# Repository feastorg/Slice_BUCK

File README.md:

# Buck Converter / Analog Signal Generator Slice

Buck Converter / Analog Signal Generator Slice for BREAD.

## Introduction

A programmable DC supply on one slice: a P-FET high-side buck stage takes the
backplane's 12 V bus and gives 0-12 V on J2, set over serial and regulated by the
Nano on A0.

## Ratings

| | |
|---|---|
| Input | +12 V bus through J1 (pins 2 and 9). Nothing else. |
| Output | 0-12 V on J2 (pin 1 +, pin 2 GNDPWR). In regulation up to about 11 V at 3 A; above that the stage goes to 100 % duty, 11.7 V into 4 ohm (2.9 A) in simulation. |
| Current | Up to 3 A out. At 100 % duty the bus carries the full load current, 3 A, which is the per-slot budget. |
| Switching | 31.25 kHz from the Nano's D9 (Timer1). |
| Feedback | Vout through 20.0k / 10.0k to A0, so 12 V out reads 4.00 V. |

**12 V bus only.** The gate drive is the input voltage: with Q1 on, its gate sits
about 0.7 V above ground, so Vgs is about -(Vin - 0.7 V). The DMP6023LE is rated
for +/-20 V gate-source, so this stage must not be fed from a 24 V bus. A bus
clamped at 15 V still gives -14.3 V, inside the rating.

**The output is regulated by firmware, not by the hardware.** At light load the
stage runs discontinuous and the output rises toward the input at any fixed duty:
in simulation 50 % duty gives 5.8 V into 4 ohm and 10.9 V into 1 kohm. Use SETV,
which regulates on A0. R9 (1k) keeps a minimum load so low voltages stay
regulable with nothing connected. The shortest on-time the stage makes is about
0.45 us (simulation), so with nothing else connected the lowest steady output is
about 1.4 V; SETV below that holds the average by toggling between that pulse and off.

At reset, or with no sketch running, D9 floats and Q1 stays off (R3 holds Q3 off,
R4 pulls the driver to +12 V).

## Usage

Serial at 115200 baud, one command per line:

| Command | Does |
|---|---|
| `ON` | Enable the output (resumes SETV regulation or the last SET duty). |
| `OFF` | Disable the output (D9 low, Q1 off). |
| `SETV <0-12>` | Regulate Vout to this many volts. The setpoint ramps at 5 V/s. |
| `SET <0-255>` | Open-loop duty (0-255 scaled onto the 9-bit timer); leaves SETV. |
| `SETTOP <ohm>` | Calibrate the divider's top resistor (default 20000). |
| `STATUS` | Print the state; also printed once a second. |

Over-voltage cut-off: if Vout stays above 13 V, or more than 1 V above the SETV
setpoint while the stage is still switching, for 50 ms, the output turns off and
the sketch prints `ERR: OV`. Send `ON` to restart.

## Documentation

Please refer to the [docs](/docs) for more info.

The switch stage has a SPICE check in `hardware/sim/`: run `python3 hardware/sim/check.py`
from the repo root with `kicad-cli` and `ngspice` on PATH.

---

<div align="center">
  
</div>

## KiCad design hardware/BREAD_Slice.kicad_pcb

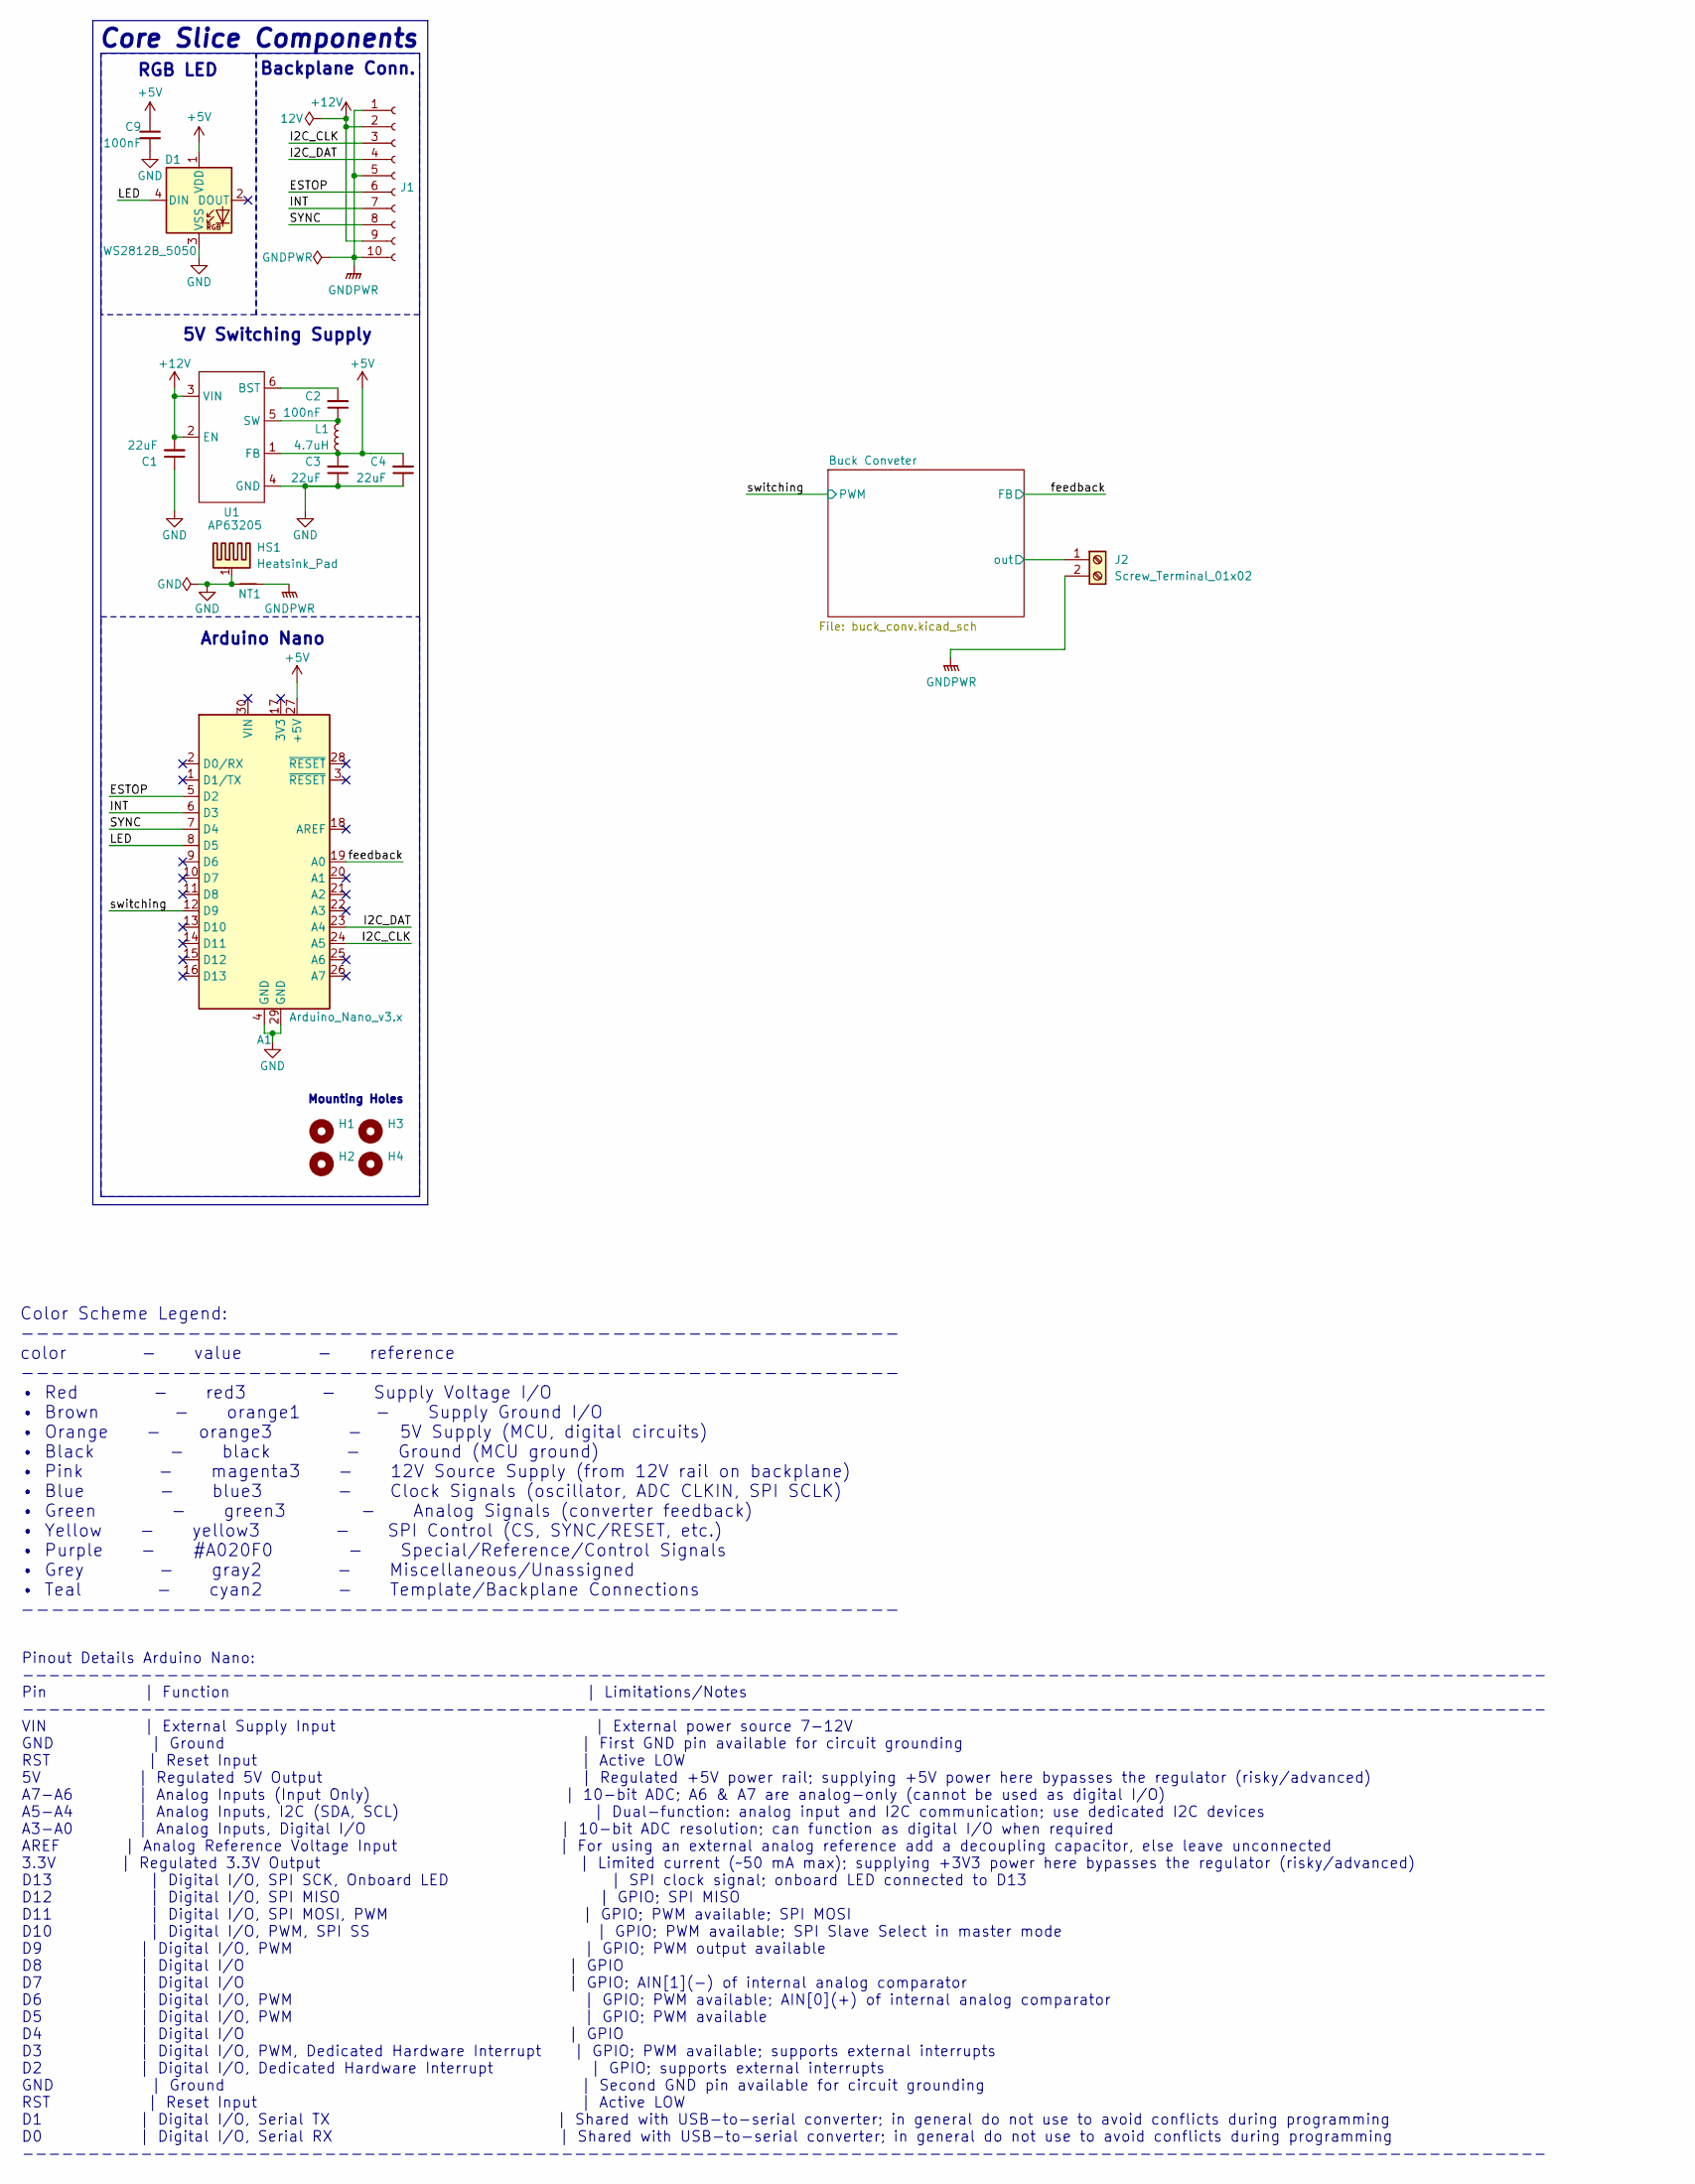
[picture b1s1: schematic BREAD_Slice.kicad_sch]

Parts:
A1: Arduino_Nano_v3.x; Arduino_Nano
C1, C3, C4: 22uF; C_1206_3216Metric
C2: 100nF; C_1206_3216Metric
C9: 100nF; C_0805_2012Metric; MPN CL21B104KBCNNNC
D1: WS2812B_5050; WS2812-5050-4PIN
H1, H2, H3, H4: MountingHole; MountingHole_5mm
HS1: Heatsink_Pad; Thermal_Pad
J1: Conn_01x10_Female; PinSocket_1x10_P2.54mm_Horizontal
J2: Screw_Terminal_01x02; TerminalBlock_4Ucon_1x02_P3.50mm_Horizontal
L1: 4.7uH; L_1210_3225Metric
NT1: NetTie_2; NetTie-2_SMD_Pad2.0mm
U1: AP63205; TSOT-23-6

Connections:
+5V: A1.27 (+5V), C3.2, C4.2, C9.1, D1.1 (VDD), L1.2, U1.1 (FB)
+12V: C1.2, J1.2, J1.9, U1.2 (EN), U1.3 (VIN); also elsewhere on the board
/Buck Conveter/out: J2.1; also elsewhere on the board
/ESTOP: A1.5 (D2), J1.6
/I2C_CLK: A1.24 (A5), J1.3
/I2C_DAT: A1.23 (A4), J1.4
/INT: A1.6 (D3), J1.7
/LED: A1.8 (D5), D1.4 (DIN)
/SYNC: A1.7 (D4), J1.8
/feedback: A1.19 (A0); also elsewhere on the board
/switching: A1.12 (D9); also elsewhere on the board
GND: A1.4 (GND), A1.29 (GND), C1.1, C3.1, C4.1, C9.2, D1.3 (VSS), HS1.1, NT1.1, U1.4 (GND); also elsewhere on the board
GNDPWR: J1.1, J1.5, J1.10, J2.2, NT1.2; also elsewhere on the board
unnamed: C2.2, U1.6 (BST)
unnamed: C2.1, L1.1, U1.5 (SW)

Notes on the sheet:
5V Switching Supply
Pinout Details Arduino Nano: -------------------------------------------------------------------------------------------------------------------- Pin | Function | Limitations/Notes -------------------------------------------------------------------------------------------------------------------- V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
RGB LED
Color Scheme Legend: ---------------------------------------------------------- color - value - reference ---------------------------------------------------------- • Red - red3 - Supply Voltage I/O • Brown - orange1 - Supply Ground I/O • Orange - orange3 - 5V Supply (MCU, digital circuits) • Black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
Core Slice Components
Arduino Nano
Mounting Holes
Backplane Conn.

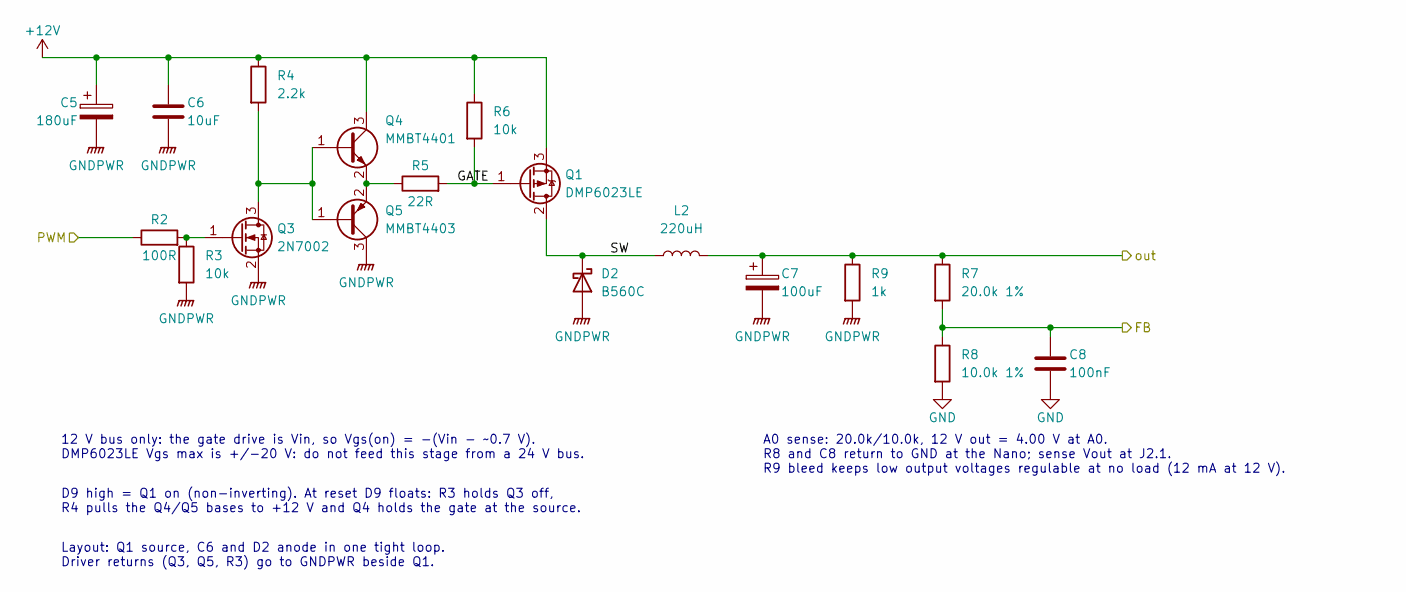
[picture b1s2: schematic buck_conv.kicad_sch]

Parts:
C5: 180uF; C_Radial_D8.0mm_H11.5mm_P3.50mm; MPN RNU1E181MDN1
C6: 10uF; C_1206_3216Metric; MPN GRM31CR71E106KA12L
C7: 100uF; C_Radial_D8.0mm_H11.5mm_P3.50mm
C8: 100nF; C_0805_2012Metric; MPN CL21B104KBCNNNC
D2: B560C; D_SMC; MPN B560C-13-F
L2: 220uH; L_Radial_D27.9mm_P19.05mm_Vishay_IHB-3; MPN 1130-221K-RC
Q1: DMP6023LE; SOT-223-3_TabPin2; MPN DMP6023LE-13
Q3: 2N7002; SOT-23; MPN 2N7002-7-F
Q4: MMBT4401; SOT-23; MPN MMBT4401-7-F
Q5: MMBT4403; SOT-23; MPN MMBT4403-7-F
R2: 100R; R_0805_2012Metric; MPN RC0805FR-07100RL
R3, R6: 10k; R_0805_2012Metric; MPN RC0805FR-0710KL
R4: 2.2k; R_1206_3216Metric; MPN RC1206FR-072K2L
R5: 22R; R_0805_2012Metric; MPN RC0805FR-0722RL
R7: 20.0k 1%; R_0805_2012Metric; MPN RC0805FR-0720KL
R8: 10.0k 1%; R_0805_2012Metric; MPN RC0805FR-0710KL
R9: 1k; R_2010_5025Metric; MPN RC2010FK-071KL

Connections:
+12V: C5.1, C6.1, Q1.3 (S), Q4.3 (C), R4.1, R6.1; also elsewhere on the board
/Buck Conveter/GATE: Q1.1 (G), R5.2, R6.2
/Buck Conveter/SW: D2.1 (K), L2.1, Q1.2 (D)
/Buck Conveter/out: C7.1, L2.2, R7.1, R9.1; also elsewhere on the board
/feedback: C8.1, R7.2, R8.1; also elsewhere on the board
/switching: R2.1; also elsewhere on the board
GND: C8.2, R8.2; also elsewhere on the board
GNDPWR: C5.2, C6.2, C7.2, D2.2 (A), Q3.2 (S), Q5.3 (C), R3.2, R9.2; also elsewhere on the board
unnamed: Q3.3 (D), Q4.1 (B), Q5.1 (B), R4.2
unnamed: Q3.1 (G), R2.2, R3.1
unnamed: Q4.2 (E), Q5.2 (E), R5.1

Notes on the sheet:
12 V bus only: the gate drive is Vin, so Vgs(on) = -(Vin - ~0.7 V). DMP6023LE Vgs max is +/-20 V: do not feed this stage from a 24 V bus.
D9 high = Q1 on (non-inverting). At reset D9 floats: R3 holds Q3 off, R4 pulls the Q4/Q5 bases to +12 V and Q4 holds the gate at the source.
Layout: Q1 source, C6 and D2 anode in one tight loop. Driver returns (Q3, Q5, R3) go to GNDPWR beside Q1.
A0 sense: 20.0k/10.0k, 12 V out = 4.00 V at A0. R8 and C8 return to GND at the Nano; sense Vout at J2.1. R9 bleed keeps low output voltages regulable at no load (12 mA at 12 V).

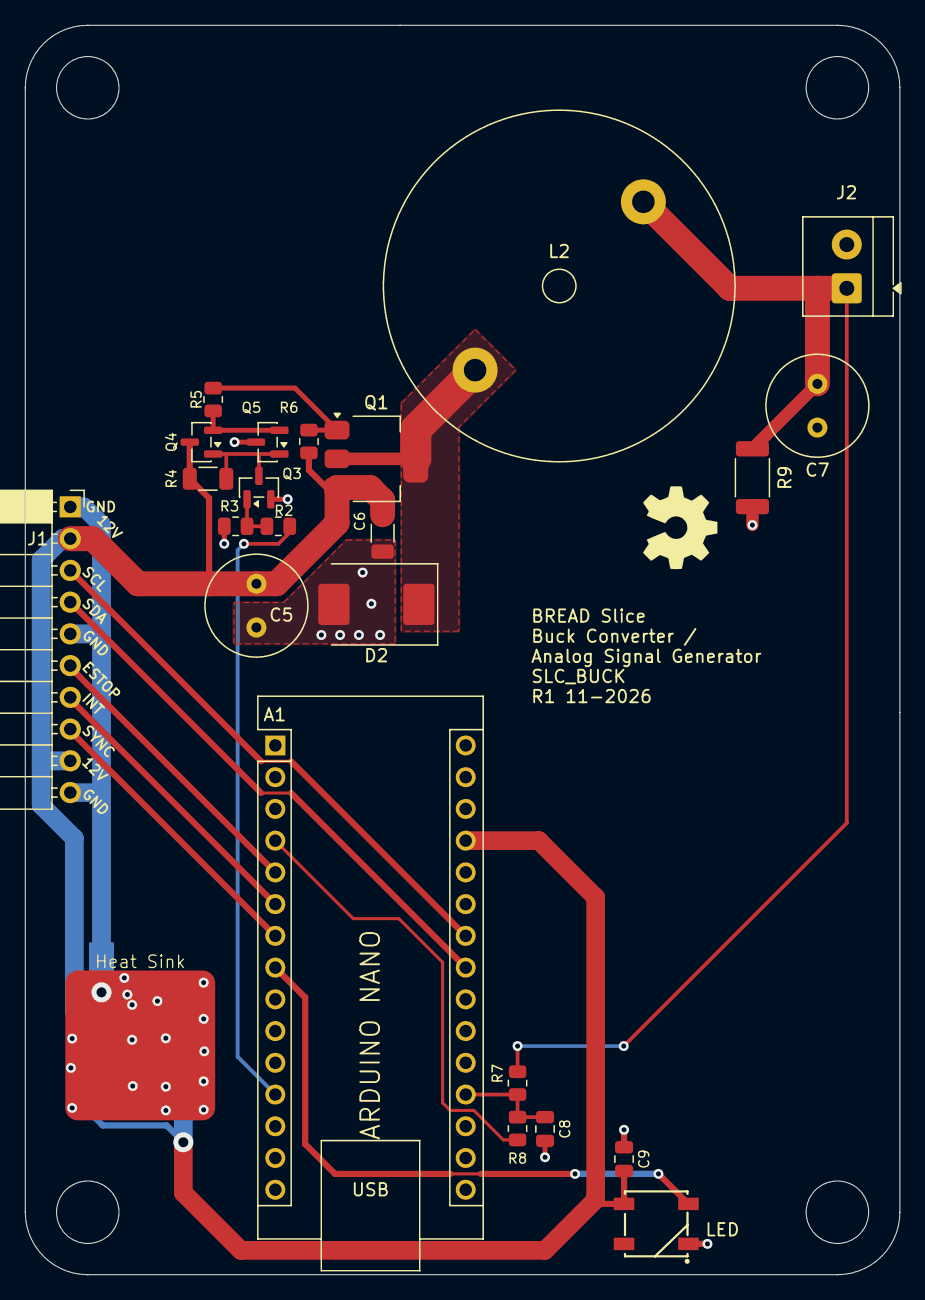
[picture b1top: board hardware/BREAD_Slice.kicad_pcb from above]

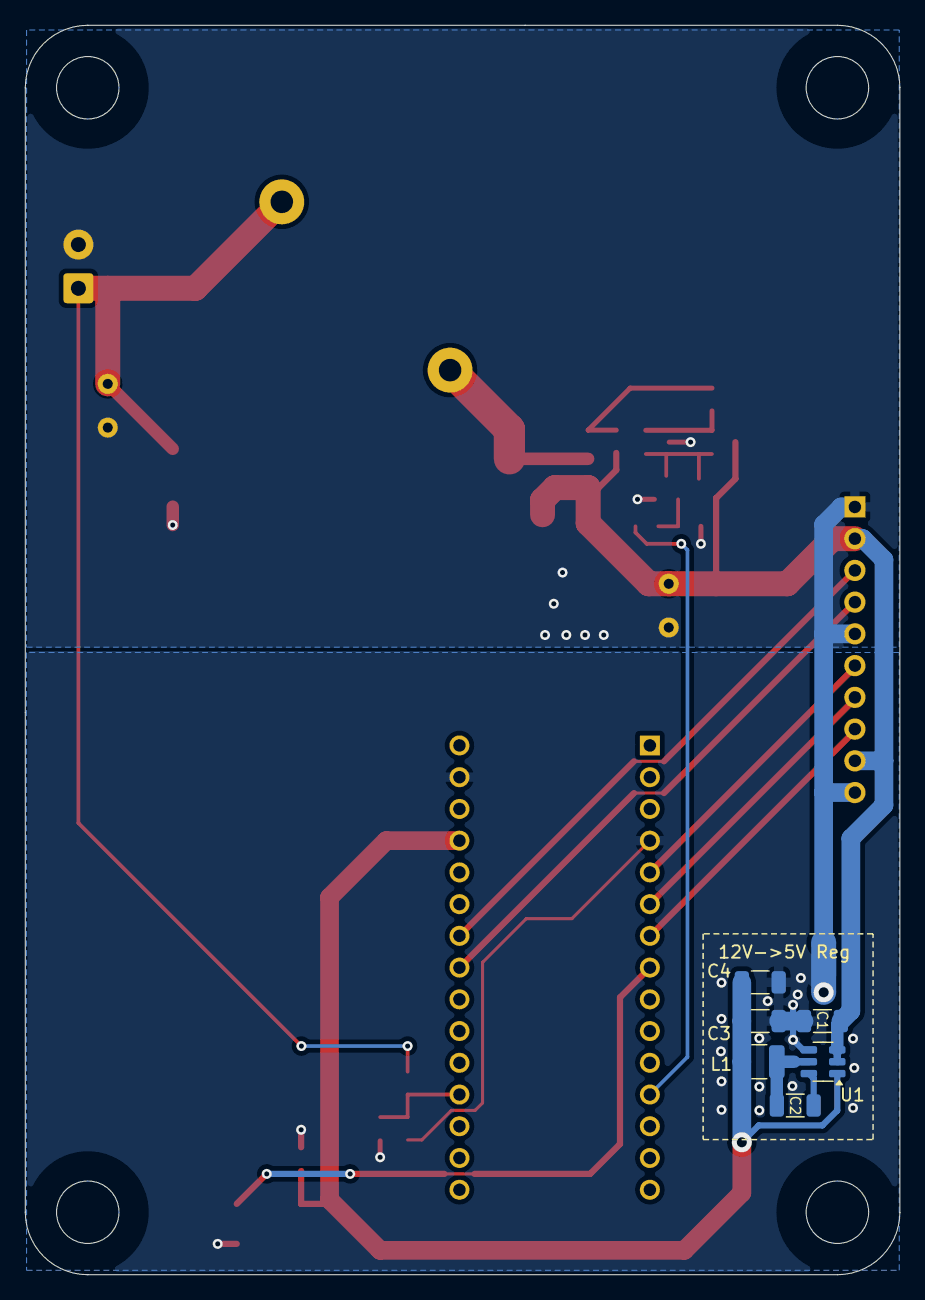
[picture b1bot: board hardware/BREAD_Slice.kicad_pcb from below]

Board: 2 copper layers, 70.0 x 100.0 mm, 36 parts (7 on the bottom side), 20 nets.

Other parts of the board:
Logo1: Logo_Open_Hardware_Small; OSHW-Symbol_6.7x6mm_SilkScreen

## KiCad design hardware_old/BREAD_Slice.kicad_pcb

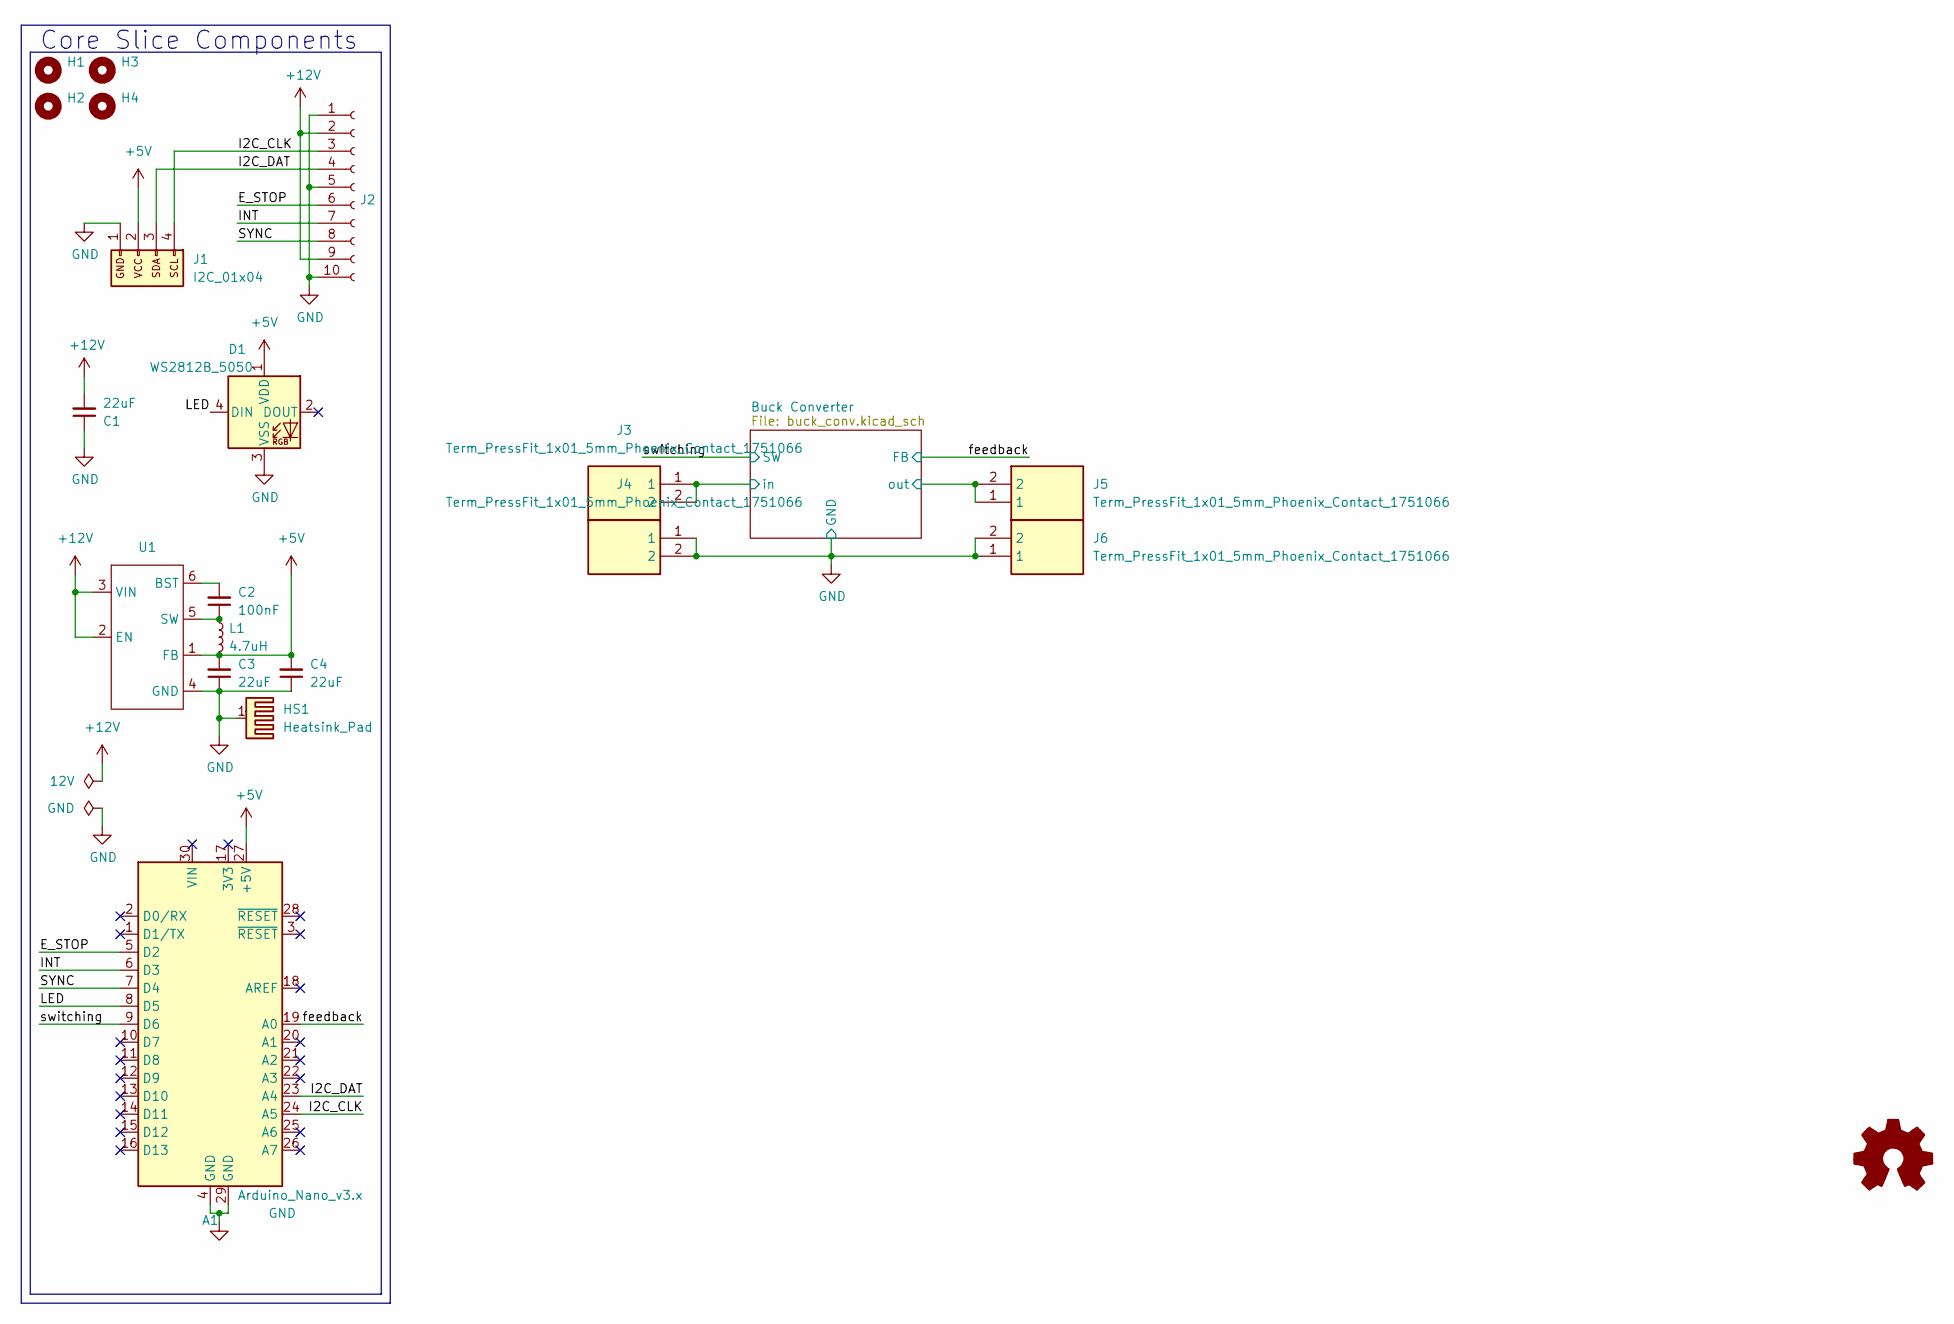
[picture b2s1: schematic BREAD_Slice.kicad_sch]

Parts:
A1: Arduino_Nano_v3.x; Arduino_Nano
C1, C3, C4: 22uF; C_1206_3216Metric
C2: 100nF; C_1206_3216Metric
D1: WS2812B_5050; WS2812-5050-4PIN
H1, H2, H3, H4: MountingHole; MountingHole_5mm
HS1: Heatsink_Pad; Thermal Pad
J1: I2C_01x04; JST_SH_SM04B-SRSS-TB_1x04-1MP_P1.00mm_Horizontal
J2: Conn_01x10_Female; PinSocket_1x10_P2.54mm_Horizontal
J3, J4, J5, J6: Term_PressFit_1x01_5mm_Phoenix_Contact_1751066; 1751066; Manufacturer_Part_Number 1751066
L1: 4.7uH; L_1210_3225Metric
U1: TSOT-23-6

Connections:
+5V: A1.27 (+5V), C3.2, C4.2, D1.1 (VDD), J1.2, L1.2, U1.1 (FB)
+12V: C1.2, J2.2, J2.9, U1.2 (EN), U1.3 (VIN)
/Buck Converter/in: J3.1, J3.2; also elsewhere on the board
/Buck Converter/out: J5.1, J5.2; also elsewhere on the board
/E_STOP: A1.5 (D2), J2.6
/I2C_CLK: A1.24 (A5), J1.4, J2.3
/I2C_DAT: A1.23 (A4), J1.3, J2.4
/INT: A1.6 (D3), J2.7
/LED: A1.8 (D5), D1.4 (DIN)
/SYNC: A1.7 (D4), J2.8
/feedback: A1.19 (A0); also elsewhere on the board
/switching: A1.9 (D6); also elsewhere on the board
GND: A1.4 (GND), A1.29 (GND), C1.1, C3.1, C4.1, D1.3 (VSS), HS1.1, J1.1, J2.1, J2.5, J2.10, J4.1, J4.2, J6.1, J6.2, U1.4 (GND); also elsewhere on the board
unnamed: C2.2, U1.6 (BST)
unnamed: C2.1, L1.1, U1.5 (SW)

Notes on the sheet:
Core Slice Components

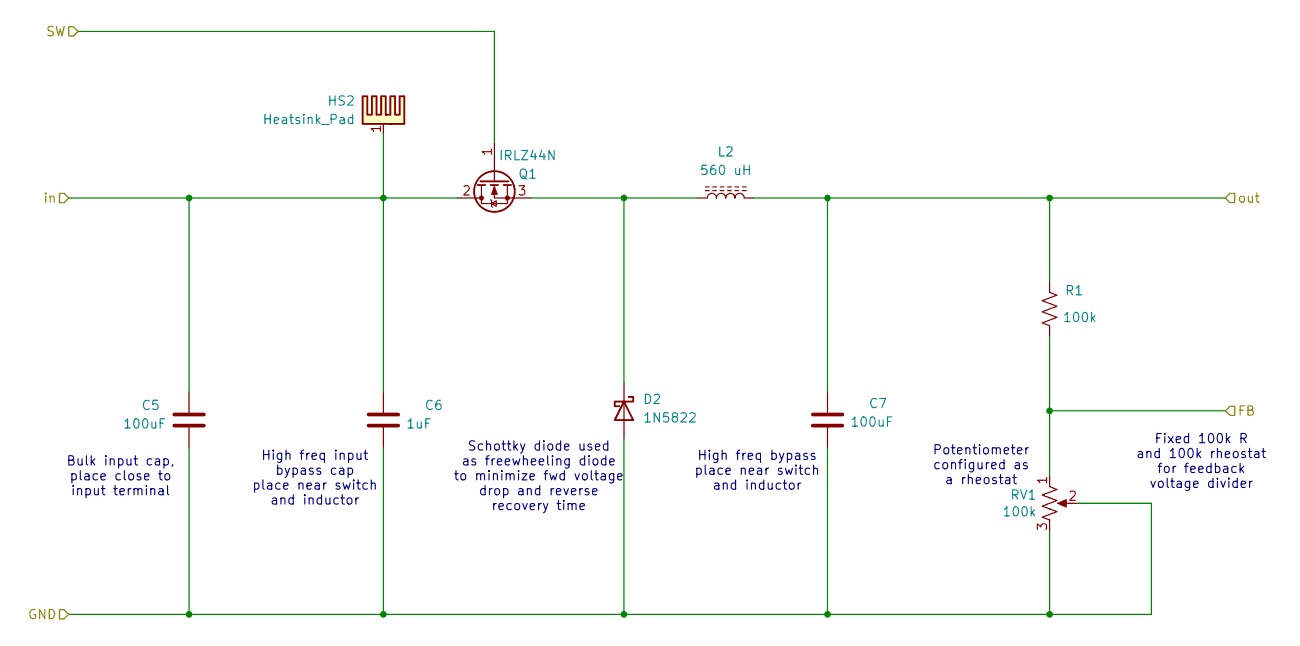
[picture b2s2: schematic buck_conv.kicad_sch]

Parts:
C5, C7: 100uF; C_Radial_D8.0mm_H11.5mm_P3.50mm
C6: 1uF; C_1206_3216Metric
D2: 1N5822; D_DO-201AD_P15.24mm_Horizontal
HS2: Heatsink_Pad; Thermal Pad
L2: 560 uH; L_Radial_D27.9mm_P19.05mm_Vishay_IHB-3
Q1: IRLZ44N; TO-220-3_Horizontal_TabDown
R1: 100k; R_Axial_DIN0309_L9.0mm_D3.2mm_P15.24mm_Horizontal
RV1: 100k; Potentiometer_Bourns_3266W_Vertical

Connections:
/Buck Converter/in: C5.1, C6.1, HS2.1, Q1.2 (D); also elsewhere on the board
/Buck Converter/out: C7.1, L2.2, R1.1; also elsewhere on the board
/feedback: R1.2, RV1.1; also elsewhere on the board
/switching: Q1.1 (G); also elsewhere on the board
GND: C5.2, C6.2, C7.2, D2.2 (A), RV1.2, RV1.3; also elsewhere on the board
unnamed: D2.1 (K), L2.1, Q1.3 (S)

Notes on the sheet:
Fixed 100k R and 100k rheostat for feedback voltage divider
Schottky diode used as freewheeling diode to minimize fwd voltage drop and reverse recovery time
Bulk input cap, place close to input terminal
High freq bypass place near switch and inductor
High freq input bypass cap place near switch and inductor
Potentiometer configured as a rheostat

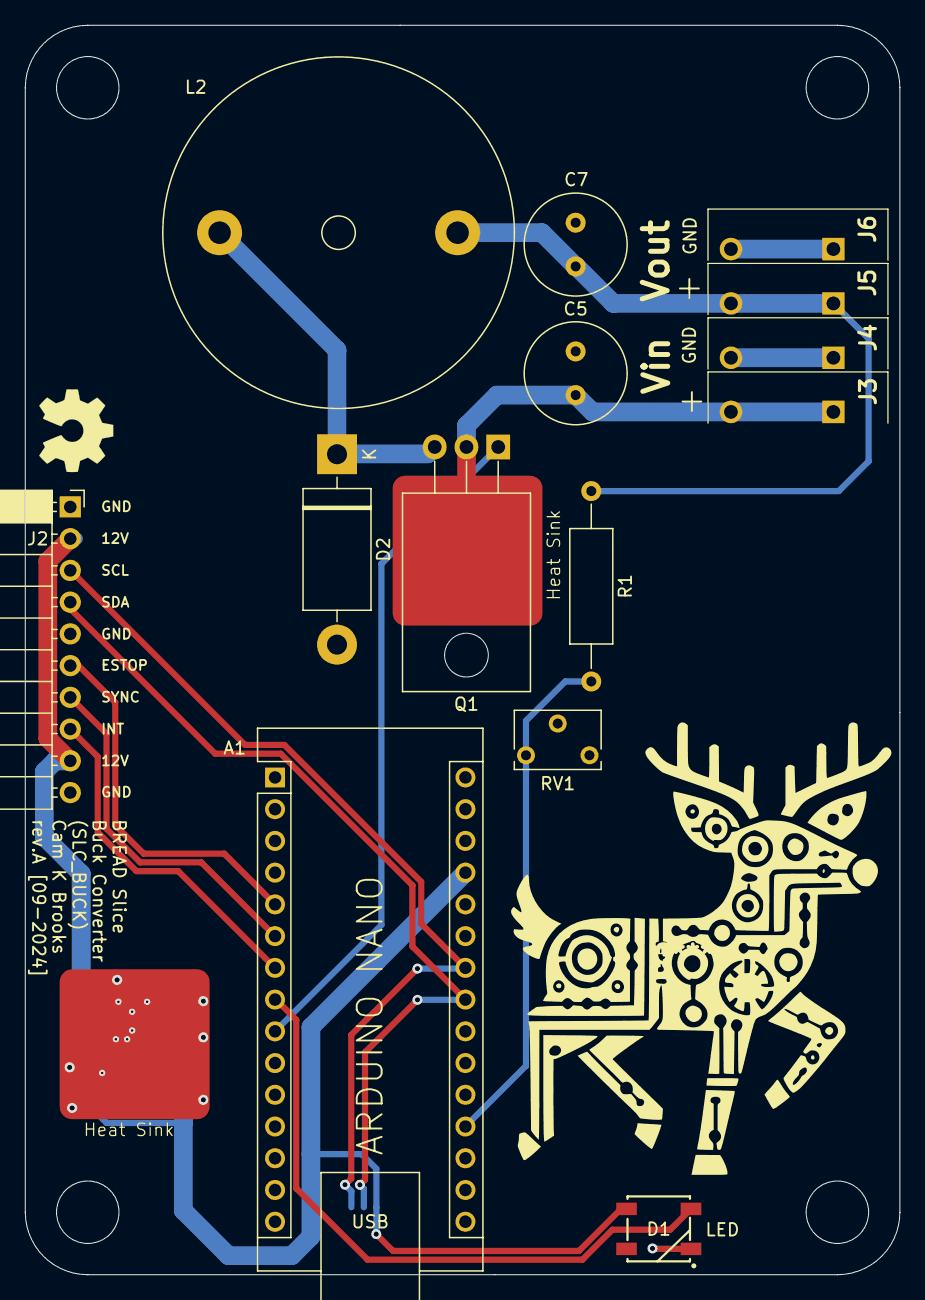
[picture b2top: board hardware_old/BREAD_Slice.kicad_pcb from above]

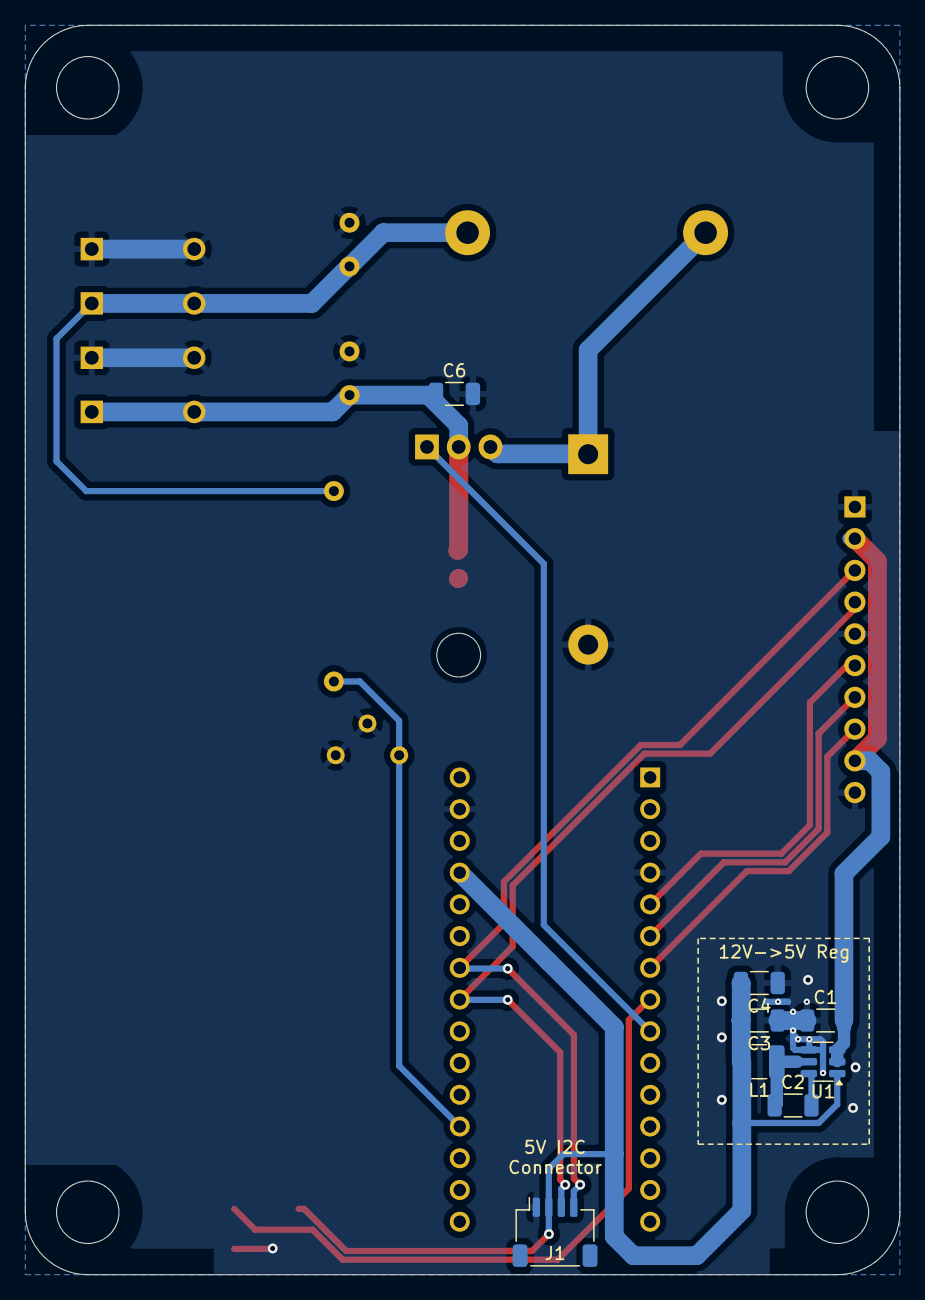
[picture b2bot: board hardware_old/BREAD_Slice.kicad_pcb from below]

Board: 2 copper layers, 70.0 x 100.0 mm, 29 parts (8 on the bottom side), 16 nets.

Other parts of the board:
Logo1: Logo_Open_Hardware_Small; OSHW-Symbol_6.7x6mm_SilkScreen

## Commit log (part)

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2024-08-16 updated to new BREAD format
2024-08-16 removed legacy hardware
2024-08-30 updated outputs for fab
2024-08-30 minor updates
2024-08-30 minor changes
2024-09-05 added art
2024-09-10 update repo
2024-09-27 cleaned up erc & drc
2024-09-30 JLCPCB order rev-A
2025-03-31 updated to use latest template
2025-03-31 removed old
2025-03-31 removed i2c conn silk
2025-04-04 finalized to 2L templ
2025-09-24 docs: add inductor part
2025-10-19 add attempt script to use current buck
2026-04-18 chore: minor updates
2026-05-20 Add slice.yaml manifest (schema v1.0)
2026-05-24 Add KiBot/docs pipeline
2026-05-24 📄 KiBot index + board renders (auto)
2026-05-24 TODO: all CI green
